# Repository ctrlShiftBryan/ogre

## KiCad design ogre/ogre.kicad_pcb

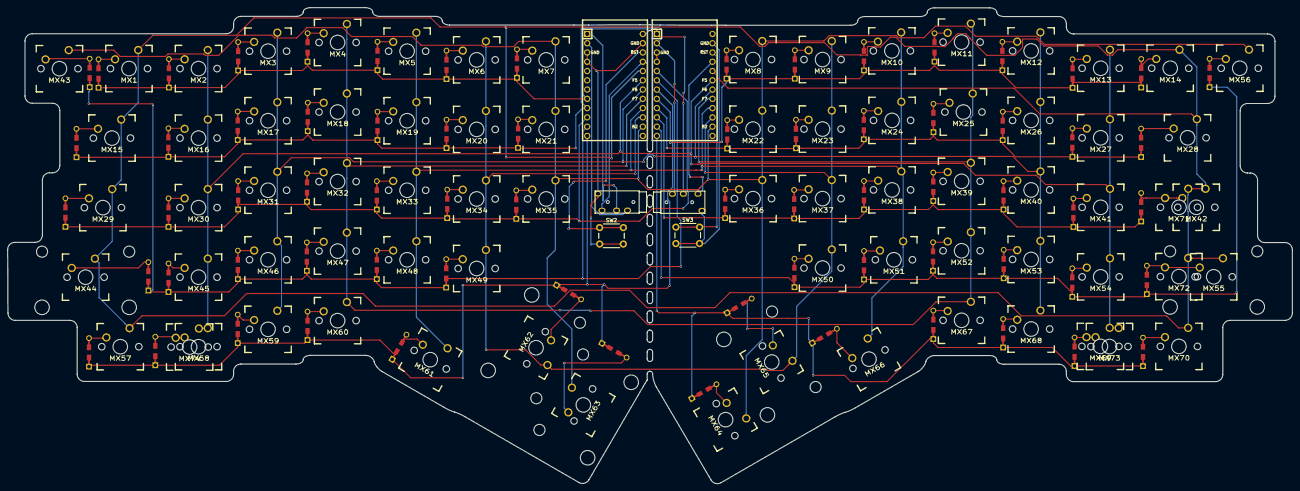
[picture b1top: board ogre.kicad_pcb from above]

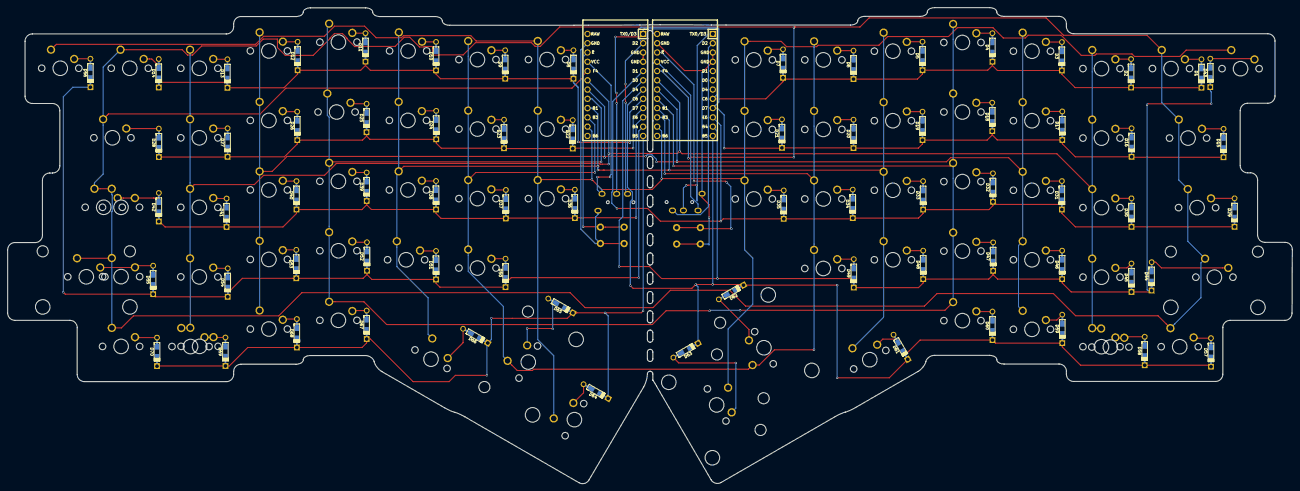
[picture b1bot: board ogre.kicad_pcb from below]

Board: 2 copper layers, 351.9 x 130.4 mm, 151 parts (70 on the bottom side), 93 nets.

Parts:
D1, D2, D3, D4, D5, D6, D7, D8, D9, D10, D11, D12, D13, D14, D15, D16, D17, D18, D19, D20, D21, D22, D23, D24, D25, D26, D27, D28, D29, D30, D31, D32, D33, D34, D35, D36, D37, D38, D39, D40, D41, D42, D43, D44, D45, D46, D47, D48, D49, D50, D51, D52, D53, D54, D55, D56, D57, D58, D59, D60, D61, D62, D63, D64, D65, D66, D67, D68, D69, D70: D_Small; Diode-dual
MX1, MX2, MX3, MX4, MX5, MX6, MX7, MX8, MX9, MX10, MX11, MX12, MX13, MX14, MX16, MX17, MX18, MX19, MX20, MX21, MX22, MX23, MX24, MX25, MX26, MX27, MX30, MX31, MX32, MX33, MX34, MX35, MX36, MX37, MX38, MX39, MX40, MX41, MX43, MX45, MX46, MX47, MX48, MX49, MX50, MX51, MX52, MX53, MX54, MX56, MX58, MX59, MX60, MX67, MX68, MX69: MX-NoLED; MX_PCB_100H
MX15, MX28: MX-NoLED; MX_PCB_150H
MX29, MX42: MX-NoLED; MX_PCB_175H
MX44, MX55, MX65: MX-NoLED; MX_PCB_225H
MX57, MX61, MX64, MX66, MX70, MX71, MX72, MX73, MX74: MX-NoLED; MX_PCB_125H
MX62: MX-NoLED; MX_PCB_275H
MX63: MX-NoLED; MX_PCB_200H
SW2, SW3: SW_Push; SW_PUSH_6mm
U2, U3: ProMicro; ArduinoProMicro
U21, U31: TRRS; TRRS-PJ-320A
ogre4-cut: ogre4-cut-2

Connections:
Col0: MX1.1, MX14.1, MX15.1, MX28.1, MX29.1, MX42.1, MX44.1, MX55.1, MX57.1, MX70.1, MX71.1, MX72.1, U2.20, U3.20
Col1: MX2.1, MX13.1, MX16.1, MX27.1, MX30.1, MX41.1, MX45.1, MX54.1, MX58.1, MX69.1, MX73.1, MX74.1, U2.19, U3.19
Col2: MX3.1, MX12.1, MX17.1, MX26.1, MX31.1, MX40.1, MX46.1, MX53.1, MX59.1, MX68.1, U2.18, U3.18
Col3: MX4.1, MX11.1, MX18.1, MX25.1, MX32.1, MX39.1, MX47.1, MX52.1, MX60.1, MX67.1, U2.17, U3.17
Col4: MX5.1, MX10.1, MX19.1, MX24.1, MX33.1, MX38.1, MX48.1, MX51.1, MX61.1, MX66.1, U2.16, U3.16
Col5: MX6.1, MX9.1, MX20.1, MX23.1, MX34.1, MX37.1, MX49.1, MX50.1, MX62.1, MX65.1, U2.15, U3.15
Col6: MX7.1, MX8.1, MX21.1, MX22.1, MX35.1, MX36.1, MX43.1, MX56.1, MX63.1, MX64.1, U2.14, U3.14
GND: SW2.2, SW3.2, U2.3, U2.4, U2.23, U3.3, U3.4, U3.23, U21.1, U31.1
unnamed: D1.2, MX1.2
unnamed: D2.2, MX2.2
unnamed: D3.2, MX3.2
unnamed: D4.2, MX4.2
unnamed: D5.2, MX5.2
unnamed: D6.2, MX6.2
unnamed: D7.2, MX7.2
unnamed: D8.2, MX8.2
unnamed: D9.2, MX9.2
unnamed: D10.2, MX10.2
unnamed: D11.2, MX11.2
unnamed: D12.2, MX12.2
unnamed: D13.2, MX13.2
unnamed: D14.2, MX14.2
unnamed: D15.2, MX15.2
unnamed: D16.2, MX16.2
unnamed: D17.2, MX17.2
unnamed: D18.2, MX18.2
unnamed: D19.2, MX19.2
unnamed: D20.2, MX20.2
unnamed: D21.2, MX21.2
unnamed: D22.2, MX22.2
unnamed: D23.2, MX23.2
unnamed: D24.2, MX24.2
unnamed: D25.2, MX25.2
unnamed: D26.2, MX26.2
unnamed: D27.2, MX27.2
unnamed: D28.2, MX28.2
unnamed: D29.2, MX29.2
unnamed: D30.2, MX30.2
unnamed: D31.2, MX31.2
unnamed: D32.2, MX32.2
unnamed: D33.2, MX33.2
unnamed: D34.2, MX34.2
unnamed: D35.2, MX35.2
unnamed: D36.2, MX36.2
unnamed: D37.2, MX37.2
unnamed: D38.2, MX38.2
unnamed: D39.2, MX39.2
unnamed: D40.2, MX40.2
unnamed: D41.2, MX41.2
unnamed: D42.2, MX42.2, MX71.2
unnamed: D43.2, MX43.2
unnamed: D44.2, MX44.2
unnamed: D45.2, MX45.2
unnamed: D46.2, MX46.2
unnamed: D47.2, MX47.2
unnamed: D48.2, MX48.2
unnamed: D49.2, MX49.2
unnamed: D50.2, MX50.2
unnamed: D51.2, MX51.2
unnamed: D52.2, MX52.2
unnamed: D53.2, MX53.2
unnamed: D54.2, MX54.2
unnamed: D55.2, MX55.2, MX72.2
unnamed: D56.2, MX56.2
unnamed: D57.2, MX57.2
unnamed: D58.2, MX58.2, MX74.2
unnamed: D59.2, MX59.2
unnamed: D60.2, MX60.2
unnamed: D61.2, MX61.2
unnamed: D62.2, MX62.2
unnamed: D63.2, MX63.2
unnamed: D64.2, MX64.2
unnamed: D65.2, MX65.2
unnamed: D66.2, MX66.2
unnamed: D67.2, MX67.2
unnamed: D68.2, MX68.2
unnamed: D69.2, MX69.2, MX73.2
unnamed: D70.2, MX70.2
RSTL: SW2.1, U2.22
RSTR: SW3.1, U3.22
Row0: D1.1, D2.1, D3.1, D4.1, D5.1, D6.1, D7.1, U2.8, U3.1, U31.3
Row1: D15.1, D16.1, D17.1, D18.1, D19.1, D20.1, D21.1, U2.9, U3.2, U31.4
Row2: D29.1, D30.1, D31.1, D32.1, D33.1, D34.1, D35.1, U2.10, U3.5
Row3: D43.1, D44.1, D45.1, D46.1, D47.1, D48.1, D49.1, U2.11, U3.6
Row4: D57.1, D58.1, D59.1, D60.1, D61.1, D62.1, D63.1, U2.12, U3.7
Row5: D8.1, D9.1, D10.1, D11.1, D12.1, D13.1, D14.1, U3.8
Row6: D22.1, D23.1, D24.1, D25.1, D26.1, D27.1, D28.1, U3.9
Row7: D36.1, D37.1, D38.1, D39.1, D40.1, D41.1, D42.1, U3.10
Row8: D50.1, D51.1, D52.1, D53.1, D54.1, D55.1, D56.1, U3.11
Row9: D64.1, D65.1, D66.1, D67.1, D68.1, D69.1, D70.1, U3.12
SCL2: U2.1, U21.3
SDA2: U2.2, U21.4
VCC: U2.21, U3.21, U21.2, U31.2

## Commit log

2019-06-29 initial empty project
2019-06-29 grid done in schematic
2019-06-29 schema without footprints
2019-06-29 fix submodule stuff
2019-06-29 readd submodules
2019-06-30 start pcb
2019-07-01 placed
2019-07-01 start flipping diodes
2019-07-01 grids done
2019-07-01 start on pro-micros
2019-07-03 right half almost done
2019-07-04 add platemount back
2019-07-24 retrace
2019-07-24 rows and columns done
2019-07-24 only a few left
2019-07-24 done
